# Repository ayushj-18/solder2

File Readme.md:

I made a pokeball from Pokemon! 
Hi, My project is a Pokeball from Pokemon. The main functions of the pokeball is to vibrate and glow. These functions can be turned off and on together using a button. 
This is my first time building a PCB, and it was fairly challenging. I learned a lot while designing this, and I really hope to learn more about electrical components
Bill of materials-

Battery,
Resistor,
Button,
LED,
Motor,
Potentiometer

This was my first time making a pcb and I kept this project simple, and explored how circuits work!

Slack username- ayushj

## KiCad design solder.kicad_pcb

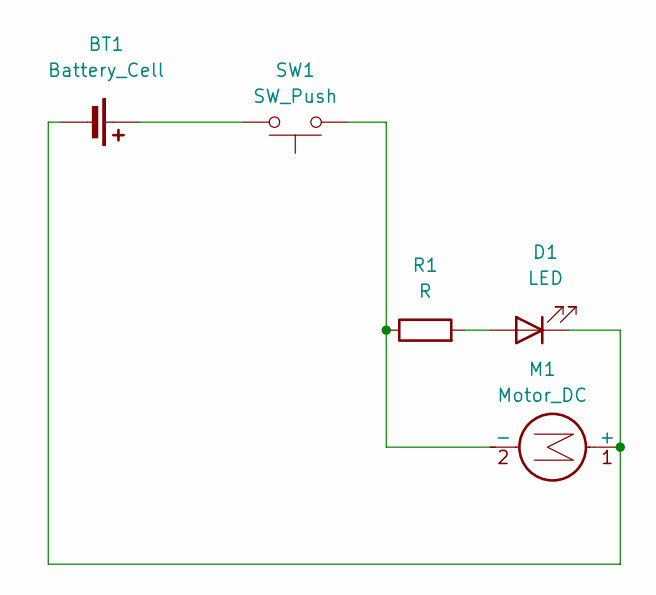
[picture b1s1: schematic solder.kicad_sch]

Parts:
BT1: Battery_Cell; BatteryHolder_Keystone_3034_1x20mm
D1: LED; LED_D5.0mm
M1: Motor_DC; PinSocket_1x02_P2.54mm_Vertical
R1: R; R_Axial_DIN0207_L6.3mm_D2.5mm_P7.62mm_Horizontal
SW1: SW_Push; SW_PUSH_6mm

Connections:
unnamed: BT1.1 (+), SW1.2
unnamed: BT1.2 (-), D1.1 (K), M1.1 (+)
unnamed: D1.2 (A), R1.2
unnamed: M1.2 (-), R1.1, SW1.1

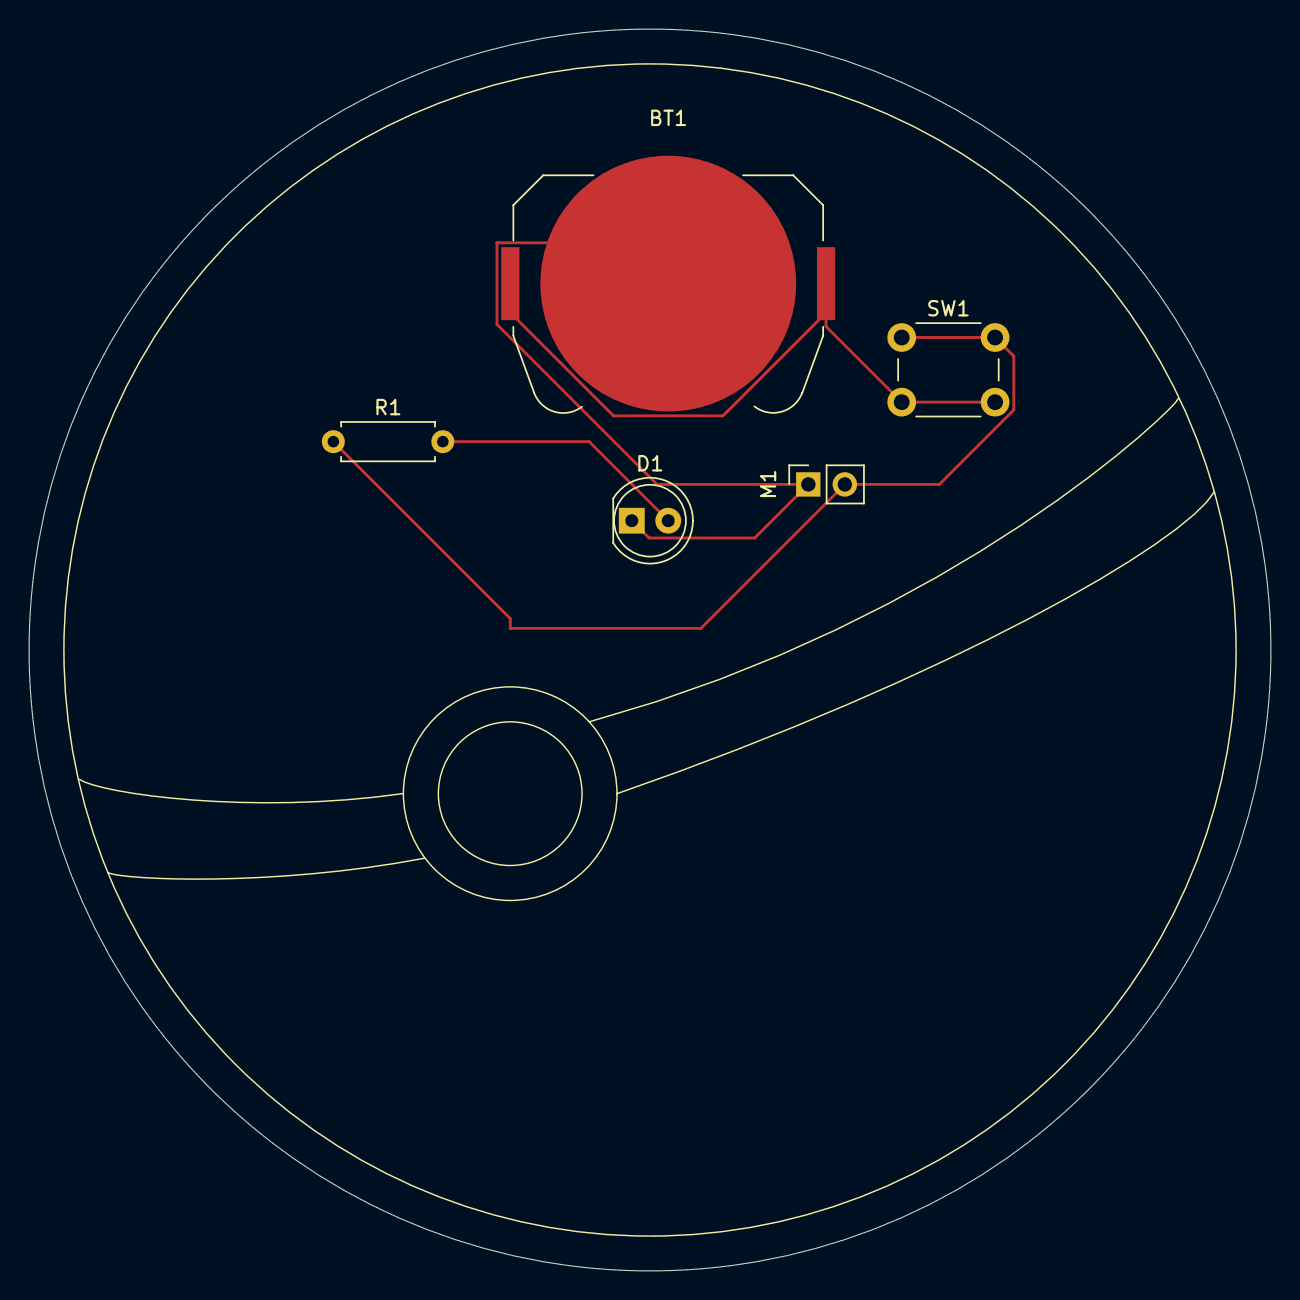
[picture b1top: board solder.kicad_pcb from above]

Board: 2 copper layers, 86.4 x 86.4 mm, 5 parts (0 on the bottom side), 4 nets.

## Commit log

2025-05-05 Update Readme.md 2
2025-05-05 Update Readme.md 3
